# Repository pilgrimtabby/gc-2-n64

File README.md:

# gc-2-n64

PCB and custom firmware for a gamecube to N64 controller adapter. The firmware is an updated version of [Raphaël Assenat's](https://github.com/raphnet)'s v2.1 gc_to_n64 software ([here](https://www.raphnet.net/electronique/gc_to_n64/index_en.php), see also [here](https://github.com/raphnet/gc_to_n64)). It implements two major new features: an input viewer (from the USB port on the Arduino, compatible with RetroSpy) and a notch calibrator (heavily adapted from [Zenith Labs' algorithm](https://github.com/ZenithControlLabs/Zenith_FW)). It also allows many more degrees of flexibility when configuring soft triggers -- triggers can be mapped at 5% press, 10% press, 15% press, and so on until 100%. 

I have also included a file ([generate-button-map.html](generate-button-map.html)) that allows users to generate custom button mappings locally. Download the file and run it in a web browser to use it.

The PCB design was heavily inspired by and drawn from [SuperSpongo's DIY adapter design](https://circuit-board.de/forum/index.php/Thread/28130-Raphnets-GameCube-Controller-to-N64-Adapter-v2/). And as mentioned before, the credit for 99% of the ideas and code goes to Raphnet, Zenith Labs, and SuperSpongo. Because I modified firmware licensed under the GPLv3 License, the code in src/ is licensed under the GPLv3 License. The PCB is licensed under the MIT license.

# Instructions

## Assembly

This project requires an Arduino Nano (though I believe any Arduino running at 5V/16MHz should work) and a DC-DC 2V-24V to 5V-28V step-up converter (the N64 provides 3.3V and we need 5V to power the Gamecube controller). You'll also need a 1KΩ resistor (R4 on the schematic), two 22Ω resistors (R1 and R3), a 220Ω resistor (R2), an LED (D1), a male N64 controller port / cable, and a female Gamecube port / cable.

(Note: If you want to modify the KiCad files, you'll need the schematic and footprint files for the boost converter found [here](pcb/kicad/gc_2_n64/boost-converter-files)).

The step-up converter needs to be calibrated to output exactly 5V when receiving 3.3V. You can do this by connecting it to a 3.3V source, such as the N64, then turning the screw on the side until the output is correct.

When soldering the wires from the Gamecube in and N64 out, follow the labels in this image:

For the N64 pinout, see [here](https://consolemods.org/wiki/N64:Connector_Pinouts). Generally, the red cable is power, white is data, and black is ground.

Gamecube pinouts are all over the place depending on which vendor you purchase from. The best resource I am aware of is [this one](https://docs.google.com/spreadsheets/d/1X-F21F838uQRCuYsc7nQoAv6I2dchvXtBSNTf-ZOc9M).

## Example of Finished Project

The assembled PCB:

The LED indicator:

Final product:

## Flashing

To flash the Arduino, you will need [avrdude](https://github.com/avrdudes/avrdude) and the latest gc_2_n64.hex hexfile (see [Releases](https://github.com/pilgrimtabby/gc-2-n64/releases)). I successfully flashed the firmware using this command:

```
/path/to/avrdude /path/to/avrdude.conf -v -V -p atmega328p -c arduino -P /path/to/serial/port -b115200 -D -U flash:w:/path/to/hexfile
```

The path to the serial port can be obtained from the [Arduino IDE](https://www.arduino.cc/en/software/).

For detailed usage of the firmware, see Raphnet's [instructions](https://www.raphnet.net/electronique/gc_to_n64/index_en.php#8). To use the new input display, just connect the Arduino to your PC via the Arduino's USB port. To use the notch calibrator, hold down the start button for 8 seconds to access the menu, then press R, then press Y. Leave the control stick at neutral and press A. The LED will blink. Do the same thing for the eight notches, starting with straight up and moving clockwise around the gate. The mapping will be saved between sessions. To clear it, press A in the R menu.

Questions, issues, PRs, etc. more than welcome!

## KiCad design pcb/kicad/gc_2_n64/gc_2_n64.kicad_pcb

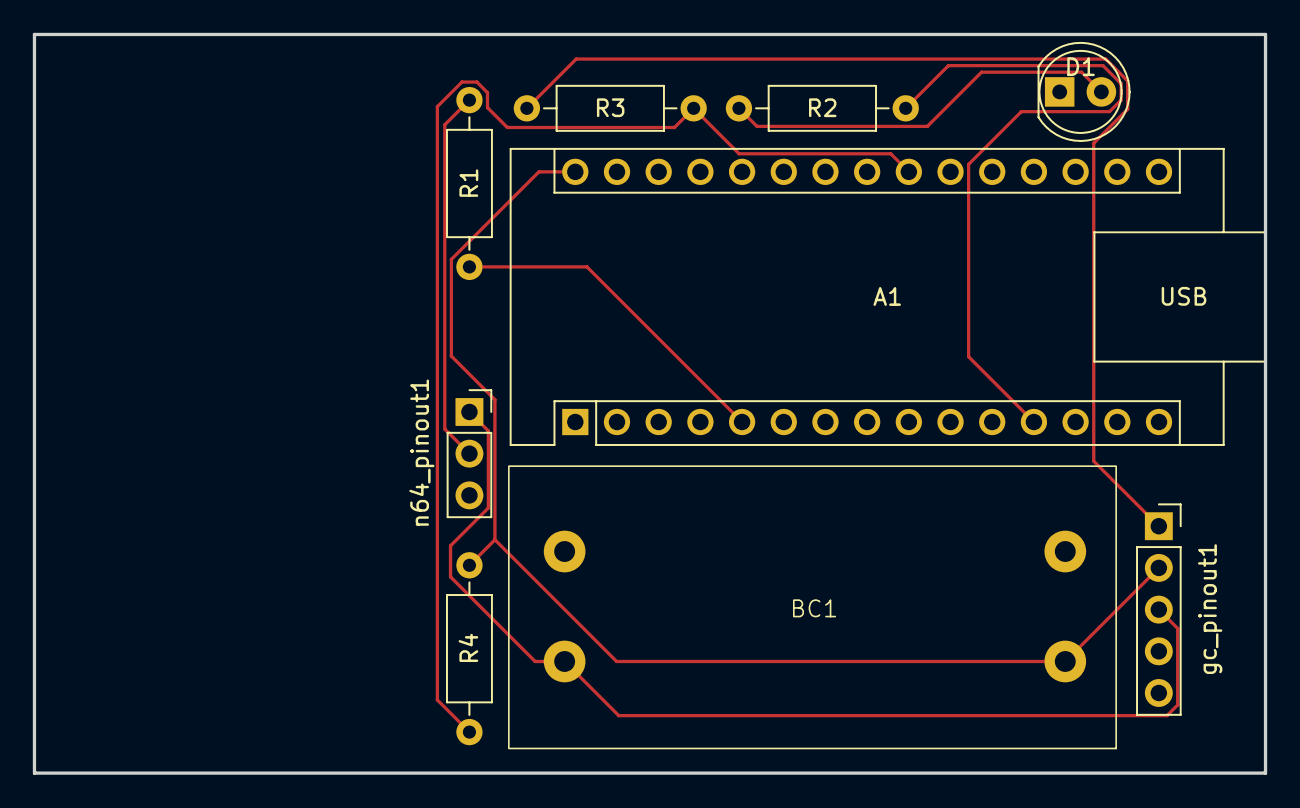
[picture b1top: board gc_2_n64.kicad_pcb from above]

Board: 2 copper layers, 75.0 x 45.0 mm, 9 parts (0 on the bottom side), 9 nets.

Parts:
A1: Arduino_Nano_v3.x; Arduino_Nano
BC1: BC_boost_converter_MT3608_breakout
D1: LED; LED_D5.0mm
R1, R3: 22Ω; R_Axial_DIN0207_L6.3mm_D2.5mm_P10.16mm_Horizontal
R2: 220Ω; R_Axial_DIN0207_L6.3mm_D2.5mm_P10.16mm_Horizontal
R4: 1kΩ; R_Axial_DIN0207_L6.3mm_D2.5mm_P10.16mm_Horizontal
gc_pinout1: Conn_01x05_Pin; PinSocket_1x05_P2.54mm_Vertical
n64_pinout1: Conn_01x03_Pin; PinSocket_1x03_P2.54mm_Vertical

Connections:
+5V: A1.30 (VIN), BC1.VOUT+, R4.1, gc_pinout1.2
/gc_3.3v: BC1.VIN+, gc_pinout1.3, n64_pinout1.1
/gc_data: R3.2, gc_pinout1.1
/n64_data: R1.1, n64_pinout1.2
GND: A1.4 (GND), A1.29 (GND), BC1.VIN-, BC1.VOUT-, D1.1 (K), gc_pinout1.4, gc_pinout1.5, n64_pinout1.3
unnamed: A1.22 (A3), R3.1, R4.2
unnamed: A1.5 (D2), R1.2
unnamed: A1.12 (D9), R2.2
unnamed: D1.2 (A), R2.1

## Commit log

2025-03-25 Add gerber files
2025-03-25 Update README, add KiCad files
2025-03-25 Update README.md w/ step-up converter directions
2025-04-23 Add photos of finished product
2025-04-23 Add photos of finished project to README.md
2025-04-23 Fix rotation of interior.jpg
2026-06-21 Add custom firmware
    I adapted Raphnet's 2.1 firmware to add customizable triggers, notch calibration, and an input viewer. The makefile has also been updated to specifically target the 328P architecture, siince the soft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
2026-06-21 Update README with licensing details
    Added licensing information for firmware and PCB
2026-06-21 Fix broken file paths in README.md
2026-06-21 Add button mapping generator html file
    This file can be loaded in a web browser to create button mappings.
2026-06-21 Update README.md with html details
2026-06-26 Fix typo in README.md
